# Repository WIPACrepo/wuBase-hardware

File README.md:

# wuBase-hardware
Hardware design files for wuBase photosensor control and readout board developed for IceCube Neutrino Observatory

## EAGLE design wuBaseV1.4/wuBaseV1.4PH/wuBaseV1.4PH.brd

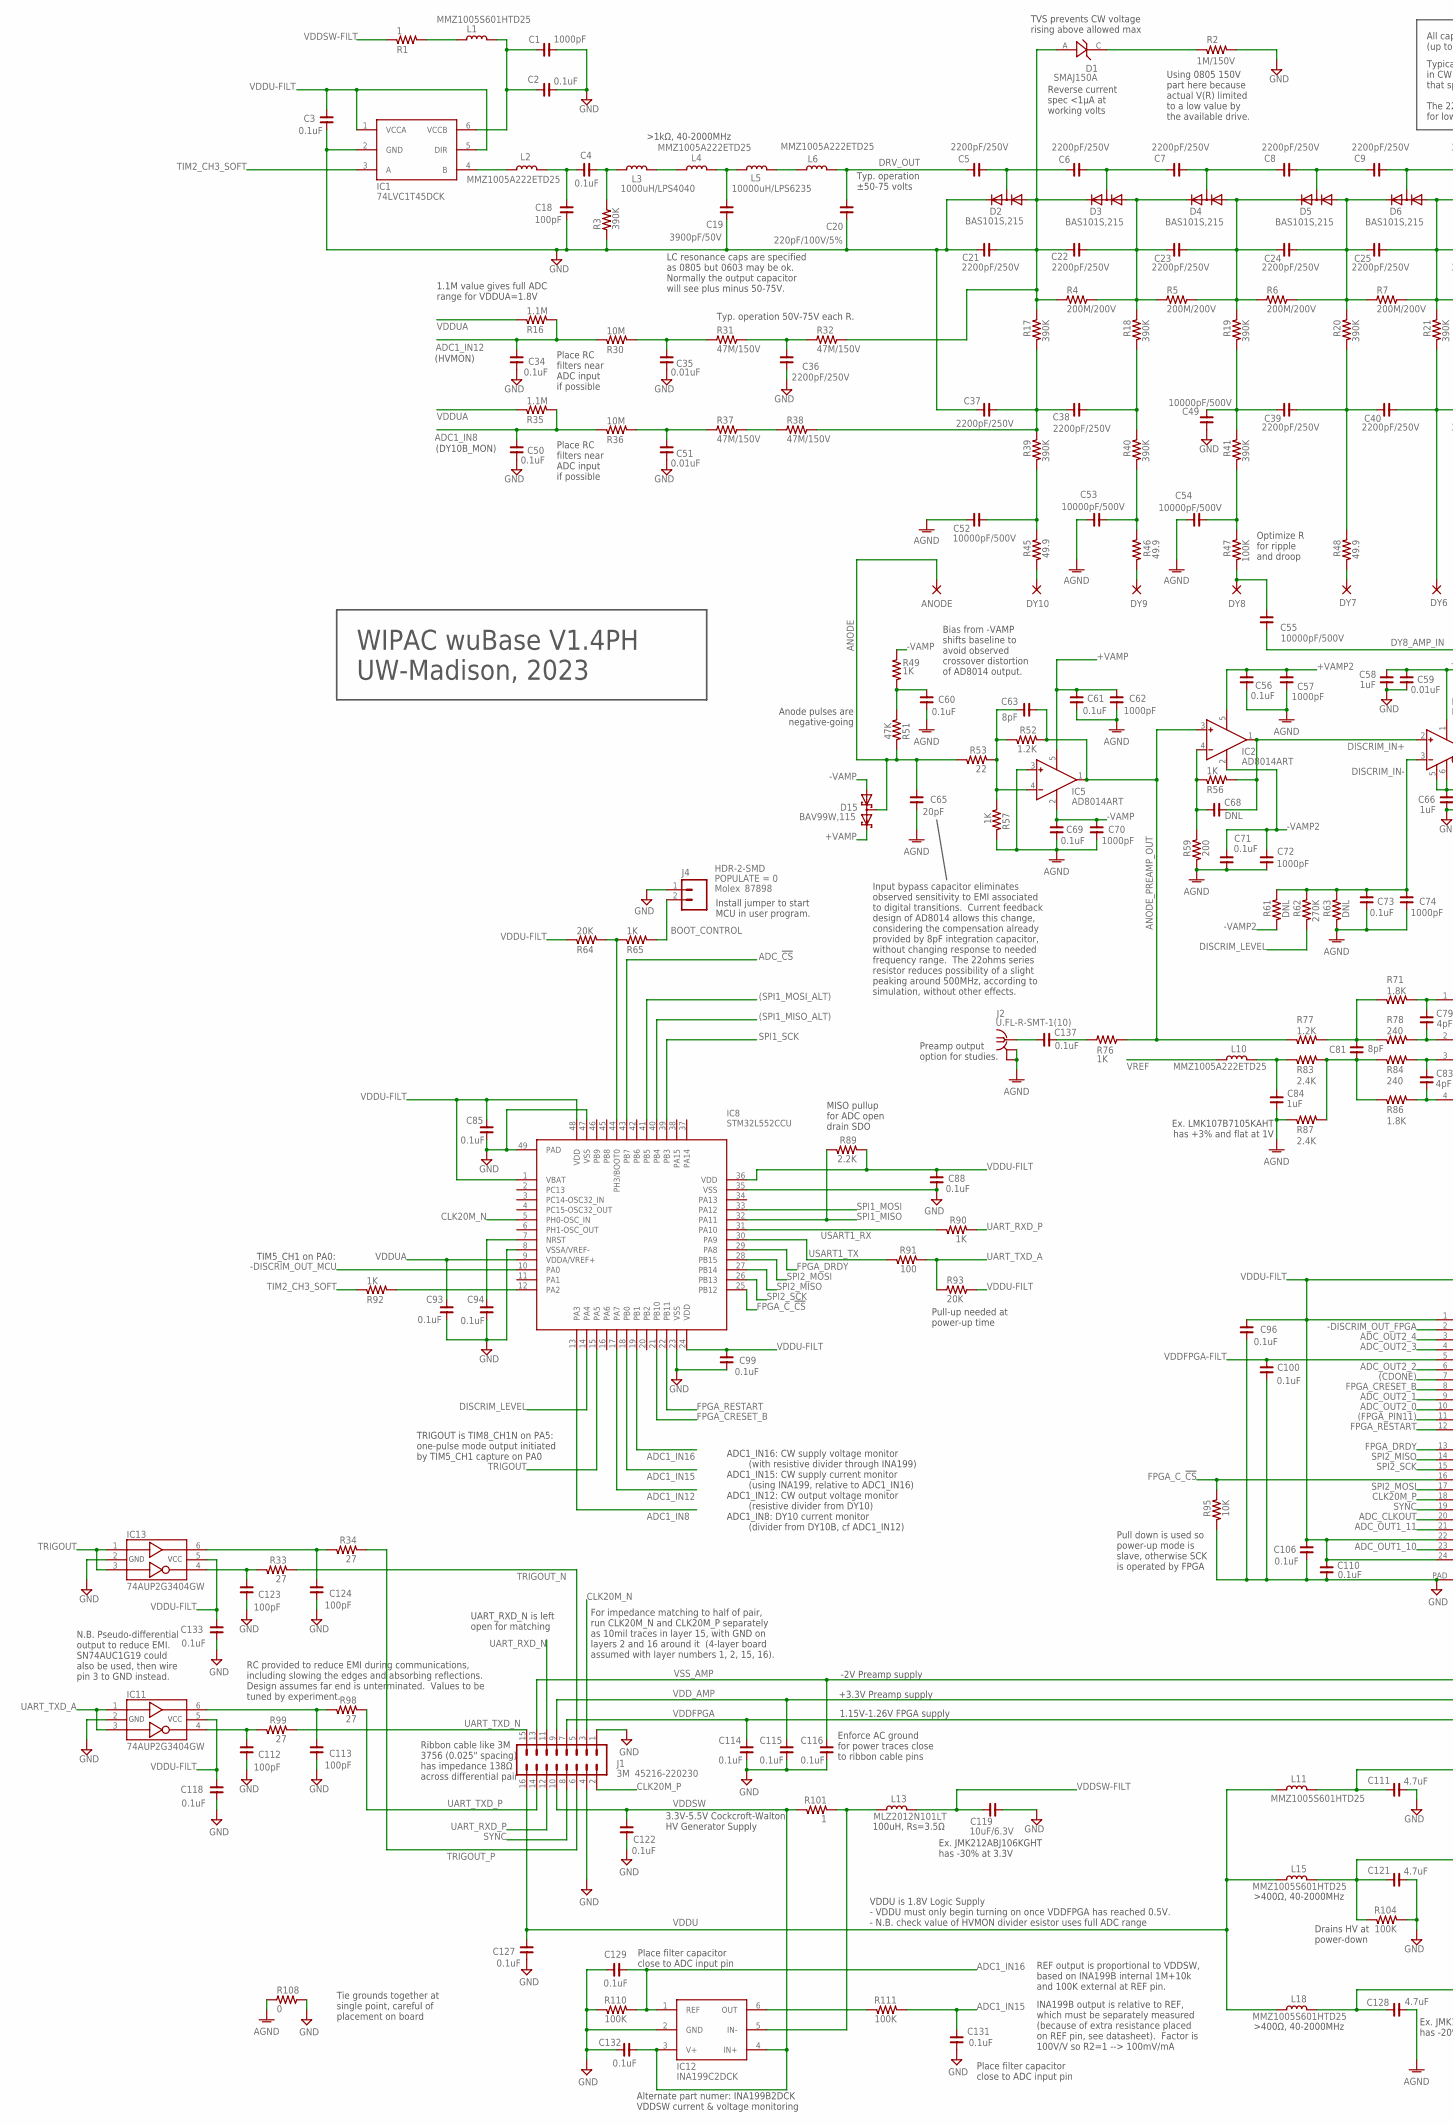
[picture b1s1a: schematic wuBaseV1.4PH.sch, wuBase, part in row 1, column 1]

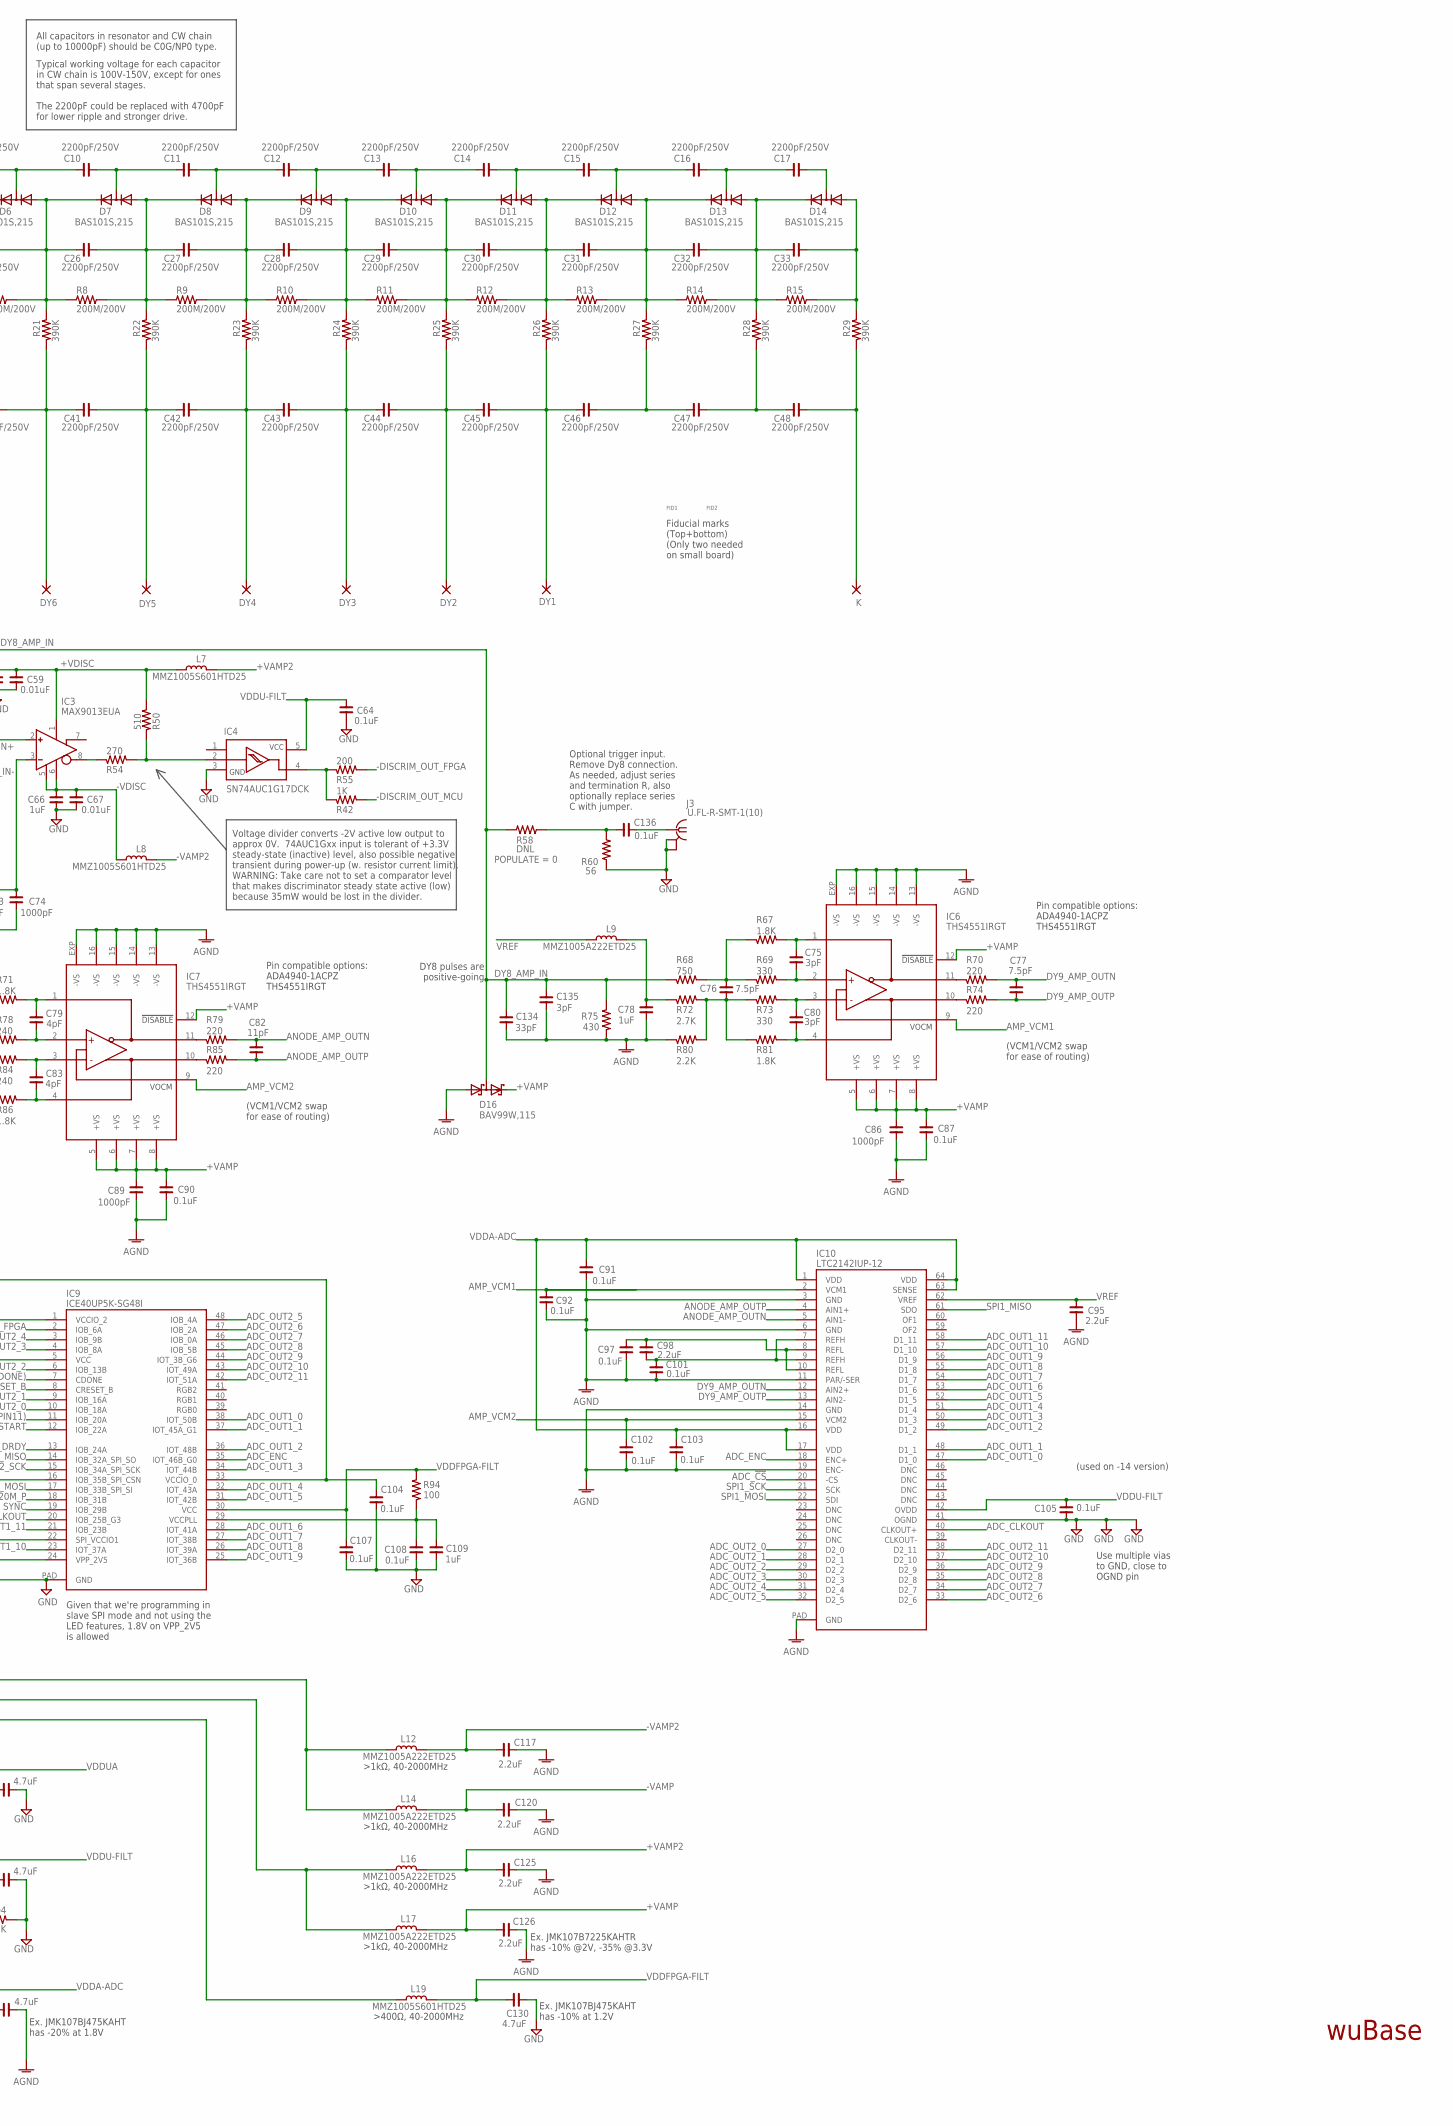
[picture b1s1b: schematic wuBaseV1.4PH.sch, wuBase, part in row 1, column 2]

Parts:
ANODE: PAD-0430-BARE; 0430-BARE
C1, C57, C62, C70, C72, C74, C86, C89: 1000pF; C0402; MPN GCM155R71H102KA37D
C2, C3, C34, C50, C56, C60, C61, C64, C69, C71, C73, C85, C87, C88, C90, C91, C92, C93, C94, C96, C97, C99, C100, C101, C102, C103, C104, C105, C106, C107, C108, C110, C114, C115, C116, C118, C122, C127, C129, C131, C132, C133, C136, C137: 0.1uF; C0402; MPN GCM155R71C104KA55D
C4: 0.1uF; C0402-HV; MPN GCM155R71C104KA55D
C5, C6, C7, C8, C9, C10, C11, C12, C13, C14, C15, C16, C17, C21, C22, C23, C24, C25, C26, C27, C28, C29, C30, C31, C32, C33, C36, C37, C38, C39, C40, C41, C42, C43, C44, C45, C46, C47, C48: 2200pF/250V; C0805-HV; MPN C0805C222JAGACAUTO
C18: 100pF; C0402-HV; MPN C0402C101J3GACAUTO
C19: 3900pF/50V; C0805-HV; MPN CGA4C2C0G1H392J060AA
C20: 220pF/100V/5%; C0805-HV; MPN C0805C221J1GACAUTO
C35, C51, C59, C67: 0.01uF; C0402; MPN CGA2B2X5R1E103K050BA
C49, C52, C53, C54, C55: 10000pF/500V; C1206-HV; MPN CGA5L4NP02J103J160AA
C58, C66, C78, C84, C109: 1uF; C0603; MPN LMK107B7105KAHT
C63, C81: 8pF; C0402; MPN GCM1555C1H8R0BA16D
C65: 20pF; C0402; MPN GCM1555C1H200JA16D
C68: DNL; C0402
C75, C80, C135: 3pF; C0402; MPN GCM1555C1H3R0BA16D
C76, C77: 7.5pF; C0402; MPN GCQ1555C1H7R5BB01D
C79, C83: 4pF; C0402; MPN GCM1555C1H4R0BA16D
C82: 11pF; C0402; MPN GCM1555C1H110FA16D
C95, C98, C117, C120, C125, C126: 2.2uF; C0603; MPN CGA3E1X7R0J225K080AC
C111, C121, C128, C130: 4.7uF; C0603; MPN JMK107BJ475KAHT
C112, C113, C123, C124: 100pF; C0402; MPN C0402C101J3GACAUTO
C119: 10uF/6.3V; C0805; MPN C0805C106K8PACTU
C134: 33pF; C0402; MPN GCM1555C1H330FA16D
D1: SMAJ150A; DO214AC-HV; MPN SMAJ150A
D2, D3, D4, D5, D6, D7, D8, D9, D10, D11, D12, D13, D14: BAS101S,215; SOT23-ROUNDED; MPN BAS101S,215
D15, D16: BAV99W,115; SC70-3L; MPN BAV99W,115
DY1, DY2, DY3, DY4, DY5, DY6, DY7, DY8, DY9, DY10: PAD-0430-BARE; 0430-BARE
FID1, FID2: FIDUCIAL_0.5MM
IC1: 74LVC1T45DCK; SC70-6L-TI; MPN 74LVC1T45GW-Q100H
IC2, IC5: AD8014ART; SOT23-5; MPN AD8014ARTZ-REEL7
IC3: MAX9013EUA; MSOP8; MPN MAX9013EUA+
IC4: SN74AUC1G17DCK; SC70-5L-TI; MPN SN74AUC1G17DCKR
IC6, IC7: THS4551IRGT; LFCSP16; MPN THS4551IRGTR
IC8: STM32L552CCU; UFQFPN48-STMICRO; MPN STM32L552CCU6
IC9: ICE40UP5K-SG48I; QFN48-ICE40ULTRA; MPN ICE40UP5K-SG48I
IC10: LTC2142IUP-12; QFN64-LTC214X; MPN LTC2141IUP-12
IC11, IC13: 74AUP2G3404GW; SC70-6L-TI; MPN 74AUP2G3404GW,125
IC12: INA199C2DCK; SC70-6L-TI; MPN INA199C2DCKR
J1: HDR-16; 3M-45216-220230; MPN 45216-220230
J2, J3: COAX-2GNDU.FL; HIROSE_U.FL-R-SMT-1; MPN U.FL-R-SMT-1(10)
J4: HDR-2-SMD; HEADER-SMD-2X1-MINIMUM; MPN 87898
K: PAD-0430-BARE; 0430-BARE
L1, L7, L8, L11, L15, L18, L19: MMZ1005S601HTD25; L0402; MPN MMZ1005S601ETD25
L2, L4, L6: MMZ1005A222ETD25; L0402-HV; MPN MMZ1005A222ETD25
L3: 1000uH/LPS4040; LPS4040-REDUCED; MPN LPS4040-105MRC
L5: 10000uH/LPS6235; LPS6235-REDUCED; MPN LPS6235-106MRC
L9, L10, L12, L14, L16, L17: MMZ1005A222ETD25; L0402; MPN MMZ1005A222ETD25
L13: MLZ2012N101LT; L0805; MPN MLZ2012N101LTD25
R1, R101: 1; R0402; MPN AC0402FR-071RL
R2: 1M/150V; R0805-HV; MPN AC0805FR-071ML
R3, R17, R18, R19, R20, R21, R22, R23, R24, R25, R26, R27, R28, R29, R39, R40, R41: 390K; R0402-HV; MPN AC0402FR-07390KL
R4, R5, R6, R7, R8, R9, R10, R11, R12, R13, R14, R15: 200M/200V; R1206-HV; MPN CRCW1206200MJPEAHR
R16, R35: 1.1M; R0402; MPN AC0402FR-071M1L
R30, R36: 10M; R0402; MPN AC0402FR-0710ML
R31, R32, R37, R38: 47M/150V; R0805-HV; MPN RC0805JR-0747ML
R33, R34, R98, R99: 27; R0402; MPN AC0402FR-0727RL
R42, R49, R56, R57, R65, R76, R90, R92: 1K; R0402; MPN AC0402FR-071KL
R45, R46, R48: 49.9; R0402-HV; MPN AC0402FR-0749R9L
R47: 100K; R0402-HV; MPN AC0402FR-07100KL
R50: 510; R0402; MPN AC0402FR-07510RL
R51: 47K; R0402; MPN AC0402FR-0747KL
R52, R77: 1.2K; R0402; MPN AC0402FR-071K2L
R53: 22; R0402; MPN AC0402FR-0722RL
R54: 270; R0402; MPN AC0402FR-07270RL
R55, R59: 200; R0402; MPN AC0402FR-07200RL
R58, R61, R63: DNL; R0402
R60: 56; R0402; MPN AC0402FR-0756RL
R62: 270K; R0402; MPN AC0402FR-07270KL
R64, R93: 20K; R0402; MPN AC0402FR-0720KL
R67, R71, R81, R86: 1.8K; R0402; MPN AC0402FR-071K8L
R68: 750; R0402; MPN AC0402FR-07750RL
R69, R73: 330; R0402; MPN AC0402FR-07330RL
R70, R74, R79, R85: 220; R0402; MPN AC0402FR-07220RL
R72: 2.7K; R0402; MPN AC0402FR-072K7L
R75: 430; R0402; MPN AC0402FR-07430RL
R78, R84: 240; R0402; MPN AC0402FR-07240RL
R80, R89: 2.2K; R0402; MPN AC0402FR-072K2L
R83, R87: 2.4K; R0402; MPN AC0402FR-072K4L
R91, R94: 100; R0402; MPN AC0402FR-07100RL
R95: 10K; R0402; MPN AC0402FR-0710KL
R104, R110, R111: 100K; R0402; MPN AC0402FR-07100KL
R108: 0; R0402; MPN RC0402JR-070RL

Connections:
(CDONE): IC9.7 (CDONE)
(FPGA_PIN11): IC9.11 (IOB_20A)
(SPI1_MISO_ALT): IC8.40 (PB4)
(SPI1_MOSI_ALT): IC8.41 (PB5)
+VAMP: C61.1, C62.1, C86.1, C87.1, C89.1, C90.1, C126.2, D15.2 (C2), D16.2 (C2), IC5.5 (V+), IC6.5 (+VS), IC6.6 (+VS), IC6.7 (+VS), IC6.8 (+VS), IC6.12 (!DISABLE), IC7.5 (+VS), IC7.6 (+VS), IC7.7 (+VS), IC7.8 (+VS), IC7.12 (!DISABLE), L17.2
+VAMP2: C56.1, C57.1, C125.2, IC2.5 (V+), L7.2, L16.2
+VDISC: C58.1, C59.1, IC3.1 (VCC), L7.1, R50.2
-DISCRIM_BUFOUT: IC4.4 (OUT), R42.1, R55.1
-DISCRIM_OUT: IC3.8 (QBAR), R54.1
-DISCRIM_OUT_DIVIDER: IC4.2 (IN), R50.1, R54.2
-DISCRIM_OUT_FPGA: IC9.2 (IOB_6A), R55.2
-DISCRIM_OUT_MCU: IC8.10 (PA0), R42.2
-VAMP: C69.1, C70.1, C120.2, D15.1 (A1), IC5.2 (V-), L14.2, R49.1
-VAMP2: C71.1, C72.1, C117.2, IC2.2 (V-), L8.2, L12.2, R61.2
-VDISC: C66.1, C67.1, IC3.5 (LE), IC3.6 (GND), L8.1
ADC1_IN8: C50.1, IC8.13 (PA3), R35.2, R36.1
ADC1_IN12: C34.1, IC8.17 (PA7), R16.2, R30.1
ADC1_IN15: C131.2, IC8.18 (PB0), R111.1
ADC1_IN16: C129.2, IC8.19 (PB1), IC12.1 (REF), R110.1
ADC_!CS: IC8.43 (PB7), IC10.20 (-CS)
ADC_CLKOUT: IC9.20 (IOB_25B_G3), IC10.40 (CLKOUT+)
ADC_ENC: IC9.35 (IOT_46B_G0), IC10.18 (ENC+)
ADC_OUT1_0: IC9.38 (IOT_50B), IC10.47 (D1_0)
ADC_OUT1_1: IC9.37 (IOT_45A_G1), IC10.48 (D1_1)
ADC_OUT1_2: IC9.36 (IOT_48B), IC10.49 (D1_2)
ADC_OUT1_3: IC9.34 (IOT_44B), IC10.50 (D1_3)
ADC_OUT1_4: IC9.32 (IOT_43A), IC10.51 (D1_4)
ADC_OUT1_5: IC9.31 (IOT_42B), IC10.52 (D1_5)
ADC_OUT1_6: IC9.28 (IOT_41A), IC10.53 (D1_6)
ADC_OUT1_7: IC9.27 (IOT_38B), IC10.54 (D1_7)
ADC_OUT1_8: IC9.26 (IOT_39A), IC10.55 (D1_8)
ADC_OUT1_9: IC9.25 (IOT_36B), IC10.56 (D1_9)
ADC_OUT1_10: IC9.23 (IOT_37A), IC10.57 (D1_10)
ADC_OUT1_11: IC9.21 (IOB_23B), IC10.58 (D1_11)
ADC_OUT2_0: IC9.10 (IOB_18A), IC10.27 (D2_0)
ADC_OUT2_1: IC9.9 (IOB_16A), IC10.28 (D2_1)
ADC_OUT2_2: IC9.6 (IOB_13B), IC10.29 (D2_2)
ADC_OUT2_3: IC9.4 (IOB_8A), IC10.30 (D2_3)
ADC_OUT2_4: IC9.3 (IOB_9B), IC10.31 (D2_4)
ADC_OUT2_5: IC9.48 (IOB_4A), IC10.32 (D2_5)
ADC_OUT2_6: IC9.47 (IOB_2A), IC10.33 (D2_6)
ADC_OUT2_7: IC9.46 (IOB_0A), IC10.34 (D2_7)
ADC_OUT2_8: IC9.45 (IOB_5B), IC10.35 (D2_8)
ADC_OUT2_9: IC9.44 (IOT_3B_G6), IC10.36 (D2_9)
ADC_OUT2_10: IC9.43 (IOT_49A), IC10.37 (D2_10)
ADC_OUT2_11: IC9.42 (IOT_51A), IC10.38 (D2_11)
AGND: C52.1, C53.2, C54.2, C56.2, C57.2, C60.2, C61.2, C62.2, C65.2, C69.2, C70.2, C71.2, C72.2, C73.2, C74.2, C78.2, C84.2, C86.2, C87.2, C89.2, C90.2, C91.2, C92.2, C95.2, C97.2, C101.2, C102.2, C103.2, C117.1, C120.1, C125.1, C126.1, C128.1, C134.2, C135.2, D16.1 (A1), IC5.3 (IN+), IC6.13 (-VS), IC6.14 (-VS), IC6.15 (-VS), IC6.16 (-VS), IC6.EXP (-VS), IC7.13 (-VS), IC7.14 (-VS), IC7.15 (-VS), IC7.16 (-VS), IC7.EXP (-VS), IC10.3 (GND), IC10.6 (GND), IC10.11 (PAR/-SER), IC10.14 (GND), IC10.19 (ENC-), IC10.PAD (GND), J2.2 (GND), J2.3 (GND), R57.2, R59.2, R63.2, R75.1, R80.1, R87.1, R108.1
AMP1_INM: C63.1, IC5.4 (IN-), R52.2, R53.1, R57.1
AMP2_INM: C68.1, IC2.4 (IN-), R56.1, R59.1
AMP_VCM1: C92.1, IC6.9 (VOCM), IC10.2 (VCM1)
AMP_VCM2: C102.1, IC7.9 (VOCM), IC10.15 (VCM2)
ANODE: ANODE.P$1, C65.1, D15.3 (C1A2), R51.2, R53.2
ANODE_AMP_OUTN: C82.1, IC10.5 (AIN1-), R79.2
ANODE_AMP_OUTP: C82.2, IC10.4 (AIN1+), R85.2
ANODE_PREAMP_OUT: C63.2, IC2.3 (IN+), IC5.1 (OUT), R52.1, R76.1, R77.1
BIAS_FILT: C60.1, R49.2, R51.1
BOOT0: IC8.44 (PH3/BOOT0), R64.2, R65.1
BOOT_CONTROL: J4.2, R65.2
CH1COAX: C137.1, J2.1 (SIGNAL)
CH1COAX_DC: C137.2, R76.2
CH2COAX: C136.2, J3.1 (SIGNAL)
CH2COAX_DC: C136.1, R58.1, R60.1
CLK20M_N: IC8.5 (PH0-OSC_IN), J1.3
CLK20M_P: IC9.18 (IOB_31B), J1.2
CW_1_KB: C15.2, C16.1, D12.3 (C1A2)
CW_2_1: C14.2, C15.1, D11.3 (C1A2)
CW_3_2: C13.2, C14.1, D10.3 (C1A2)
CW_4_3: C12.2, C13.1, D9.3 (C1A2)
CW_5_4: C11.2, C12.1, D8.3 (C1A2)
CW_6_5: C10.2, C11.1, D7.3 (C1A2)
CW_7_6: C9.2, C10.1, D6.3 (C1A2)
CW_8_7: C8.2, C9.1, D5.3 (C1A2)
CW_9_8: C7.2, C8.1, D4.3 (C1A2)
CW_10_9: C6.2, C7.1, D3.3 (C1A2)
CW_A_10: C5.2, C6.1, D2.3 (C1A2)
CW_KA_K: C17.2, D14.3 (C1A2)
CW_KB_KA: C16.2, C17.1, D13.3 (C1A2)
DISCRIM_IN+: C68.2, IC2.1 (OUT), IC3.2 (IN+), R56.2
DISCRIM_IN-: C73.1, C74.1, IC3.3 (IN-), R61.1, R62.1, R63.1
DISCRIM_LEVEL: IC8.14 (PA4), R62.2
DRV_FILT: C4.2, C18.1, L2.2
DRV_L1INP: C4.1, L3.2, R3.2
DRV_L1OUT: L3.1, L4.1
DRV_L2INP: C19.1, L4.2, L5.2
DRV_L2OUT: L5.1, L6.2
DRV_OUT: C5.1, C20.1, L6.1
DRV_SQUARE: IC1.4 (B), L2.1
DY1: C45.2, C46.1, DY1.P$1, R26.2
DY1A: C30.2, C31.1, D11.1 (A1), D12.2 (C2), R12.2, R13.1, R26.1
DY2: C44.2, C45.1, DY2.P$1, R25.2
DY2A: C29.2, C30.1, D10.1 (A1), D11.2 (C2), R11.2, R12.1, R25.1
DY3: C43.2, C44.1, DY3.P$1, R24.2
DY3A: C28.2, C29.1, D9.1 (A1), D10.2 (C2), R10.2, R11.1, R24.1
DY4: C42.2, C43.1, DY4.P$1, R23.2
DY4A: C27.2, C28.1, D8.1 (A1), D9.2 (C2), R9.2, R10.1, R23.1
DY5: C41.2, C42.1, DY5.P$1, R22.2
DY5A: C26.2, C27.1, D7.1 (A1), D8.2 (C2), R8.2, R9.1, R22.1
DY6: C40.2, C41.1, DY6.P$1, R21.2
DY6A: C25.2, C26.1, D6.1 (A1), D7.2 (C2), R7.2, R8.1, R21.1
DY7: DY7.P$1, R48.2
DY7A: C24.2, C25.1, D5.1 (A1), D6.2 (C2), R6.2, R7.1, R20.1
DY7B: C39.2, C40.1, R20.2, R48.1
DY8: C55.1, DY8.P$1, R47.2
DY8A: C23.2, C24.1, D4.1 (A1), D5.2 (C2), R5.2, R6.1, R19.1
DY8B: C39.1, C49.1, R19.2, R41.1
DY8C: C54.1, R41.2, R47.1
DY8_AMP_IN: C55.2, C134.1, C135.1, D16.3 (C1A2), R58.2, R68.1, R75.2
DY9: DY9.P$1, R46.2
DY9A: C22.2, C23.1, D3.1 (A1), D4.2 (C2), R4.2, R5.1, R18.1
DY9B: C38.2, R18.2, R40.1
DY9C: C53.1, R40.2, R46.1
DY9_AMP_OUTN: C77.1, IC10.12 (AIN2+), R70.2
DY9_AMP_OUTP: C77.2, IC10.13 (AIN2-), R74.2
DY10: DY10.P$1, R45.2
DY10A: C21.2, C22.1, D1.A, D2.1 (A1), D3.2 (C2), R4.1, R17.1, R32.2
DY10B: C37.2, C38.1, R17.2, R38.2, R39.1
DY10B_MON_A: R37.2, R38.1
DY10B_MON_B: C51.1, R36.2, R37.1
DY10C: C52.2, R39.2, R45.1
FPGA_CRESET_B: IC8.21 (PB10), IC9.8 (CRESET_B)
FPGA_C_!CS: IC8.25 (PB12), IC9.16 (IOB_35B_SPI_CSN), R95.1
FPGA_DRDY: IC8.29 (PA8), IC9.13 (IOB_24A)
FPGA_RESTART: IC8.22 (PB11), IC9.12 (IOB_22A)
GND: C1.1, C2.1, C3.1, C18.2, C19.2, C20.2, C21.1, C34.2, C35.2, C36.2, C37.1, C49.2, C50.2, C51.2, C58.2, C59.2, C64.1, C66.2, C67.2, C85.2, C88.2, C93.2, C94.2, C96.2, C99.2, C100.2, C104.2, C105.2, C106.2, C107.2, C108.2, C109.2, C110.2, C111.1, C112.2, C113.2, C114.2, C115.2, C116.2, C118.2, C119.2, C121.1, C122.2, C123.2, C124.2, C127.2, C129.1, C130.2, C131.1, C132.1, C133.2, D2.2 (C2), IC1.2 (GND), IC4.3 (GND), IC8.8 (VSSA/VREF-), IC8.23 (VSS), IC8.35 (VSS), IC8.47 (VSS), IC8.49 (PAD), IC9.PAD (GND), IC10.41 (OGND), IC11.2 (GND), IC12.2 (GND), IC13.2 (GND), J1.1, J1.4, J3.2 (GND), J3.3 (GND), J4.1, R2.1, R3.1, R60.2, R95.2, R104.1, R108.2, R110.2
HVMON_A: C36.1, R31.2, R32.1
HVMON_B: C35.1, R30.2, R31.1
K: C48.2, K.P$1, R29.2
K-DY1-AA: C32.2, C33.1, D13.1 (A1), D14.2 (C2), R14.2, R15.1, R28.1
K-DY1-AB: C47.2, C48.1, R28.2
K-DY1-BA: C31.2, C32.1, D12.1 (A1), D13.2 (C2), R13.2, R14.1, R27.1
K-DY1-BB: C46.2, C47.1, R27.2
KA: C33.2, D14.1 (A1), R15.2, R29.1
unnamed: C79.2, IC7.2 (+IN), R78.2
unnamed: C83.1, IC7.3 (-IN), R84.2
unnamed: C81.2, R83.2, R84.1, R86.1, R87.2
unnamed: C81.1, R71.1, R77.2, R78.1
unnamed: C79.1, IC7.1 (-FB), R71.2
unnamed: C83.2, IC7.4 (+FB), R86.2
unnamed: IC7.11 (-OUT), R79.1
unnamed: IC7.10 (+OUT), R85.1
unnamed: C75.2, IC6.2 (+IN), R69.2
unnamed: C80.1, IC6.3 (-IN), R73.2
unnamed: C76.1, R67.1, R68.2, R69.1
unnamed: C76.2, R72.2, R73.1, R80.2, R81.1
unnamed: C75.1, IC6.1 (-FB), R67.2
unnamed: C80.2, IC6.4 (+FB), R81.2
unnamed: IC6.11 (-OUT), R70.1
unnamed: IC6.10 (+OUT), R74.1
NRST: C94.1, IC8.7 (NRST)
REFH: C98.2, C101.1, IC10.7 (REFH), IC10.9 (REFH)
REFL: C97.1, C98.1, IC10.8 (REFL), IC10.10 (REFL)
SPI1_MISO: IC8.32 (PA11), IC10.61 (SDO), R89.2
SPI1_MOSI: IC8.33 (PA12), IC10.22 (SDI)
SPI1_SCK: IC8.39 (PB3), IC10.21 (SCK)
SPI2_MISO: IC8.27 (PB14), IC9.14 (IOB_32A_SPI_SO)
SPI2_MOSI: IC8.28 (PB15), IC9.17 (IOB_33B_SPI_SI)
SPI2_SCK: IC8.26 (PB13), IC9.15 (IOB_34A_SPI_SCK)
SYNC: IC9.19 (IOB_29B), J1.8
TIM2_CH3: IC8.12 (PA2), R92.2
TIM2_CH3_SOFT: IC1.3 (A), R92.1
TRIGOUT: IC8.15 (PA5), IC13.1 (1A), IC13.3 (2A)
TRIGOUT_N: J1.5, R33.1
TRIGOUT_NA: C123.1, IC13.4 (2Y), R33.2
TRIGOUT_P: J1.6, R34.1
TRIGOUT_PA: C124.1, IC13.6 (1Y), R34.2
TVS_OUT: D1.C, R2.2
UART_RXD_N: J1.11
UART_RXD_P: J1.12, R90.1
UART_TXD_A: IC11.1 (1A), IC11.3 (2A), R91.1, R93.1
UART_TXD_N: J1.15, R99.1
UART_TXD_NA: C112.1, IC11.4 (2Y), R99.2
UART_TXD_P: J1.14, R98.1
UART_TXD_PA: C113.1, IC11.6 (1Y), R98.2
USART1_RX: IC8.31 (PA10), R90.2
USART1_TX: IC8.30 (PA9), R91.2
VCCPLL: C108.1, C109.1, IC9.29 (VCCPLL), R94.2
VDDA-ADC: C91.1, C103.1, C128.2, IC10.1 (VDD), IC10.16 (VDD), IC10.17 (VDD), IC10.63 (SENSE), IC10.64 (VDD), L18.2
VDDFPGA: C114.1, J1.7, L19.1
VDDFPGA-FILT: C100.1, C107.1, C130.1, IC9.5 (VCC), IC9.30 (VCC), L19.2, R94.1
VDDSW: C122.1, C132.2, IC12.3 (V+), IC12.4 (IN+), J1.10, R101.2
VDDSW-FILT: C119.1, L13.2, R1.1
VDDSW-FILT-RL: L1.2, R1.2
VDDSW-FINAL: C1.2, C2.2, IC1.6 (VCCB), L1.1
VDDSW-RL: IC12.5 (IN-), L13.1, R101.1
VDDSW_IMON: IC12.6 (OUT), R111.2
VDDU: C127.1, J1.16, L11.1, L15.1, L18.1
VDDU-FILT: C3.2, C64.2, C85.1, C88.1, C96.1, C99.1, C104.1, C105.1, C106.1, C110.1, C118.1, C121.2, C133.1, IC1.1 (VCCA), IC1.5 (DIR), IC4.5 (VCC), IC8.1 (VBAT), IC8.24 (VDD), IC8.36 (VDD), IC8.48 (VDD), IC9.1 (VCCIO_2), IC9.22 (SPI_VCCIO1), IC9.24 (VPP_2V5), IC9.33 (VCCIO_0), IC10.42 (OVDD), IC11.5 (VCC), IC13.5 (VCC), L15.2, R64.1, R89.1, R93.2, R104.2
VDDUA: C93.1, C111.2, IC8.9 (VDDA/VREF+), L11.2, R16.1, R35.1
VDD_AMP: C115.1, J1.9, L16.1, L17.1
VREF: C95.1, IC10.62 (VREF), L9.1, L10.1
VREF_FILT1: C84.1, L10.2, R83.1
VREF_FILT2: C78.1, L9.2, R72.1
VSS_AMP: C116.1, J1.13, L12.1, L14.1

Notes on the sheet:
Fiducial marks (Top+bottom) (Only two needed on small board)
VDDU is 1.8V Logic Supply - VDDU must only begin turning on once VDDFPGA has reached 0.5V. - N.B. check value of HVMON divider esistor uses full ADC range
3.3V-5.5V Cockcroft-Walton HV Generator Supply
(HVMON)
INA199B output is relative to REF, which must be separately measured (because of extra resistance placed on REF pin, see datasheet). Factor is 100V/V so R2=1 --> 100mV/mA
ADC1_IN16: CW supply voltage monitor (with resistive divider through INA199) ADC1_IN15: CW supply current monitor (using INA199, relative to ADC1_IN16) ADC1_IN12: CW output voltage monitor (resistive divider from DY10) ADC1_IN8: DY10 current monitor (divider from DY10B, cf ADC1_IN12)
REF output is proportional to VDDSW, based on INA199B internal 1M+10k and 100K external at REF pin.
Place filter capacitor close to ADC input pin
Alternate part numer: INA199B2DCK VDDSW current & voltage monitoring
100uH, Rs=3.5Ω
WIPAC wuBase V1.4PH UW-Madison, 2023
TVS prevents CW voltage rising above allowed max
Place RC filters near ADC input if possible
Typ. operation 50V-75V each R.
Typ. operation ±50-75 volts
Drains HV at power-down
Typical working voltage for each capacitor in CW chain is 100V-150V, except for ones that span several stages. The 2200pF could be replaced with 4700pF for lower ripple and stronger drive.
All capacitors in resonator and CW chain (up to 10000pF) should be C0G/NP0 type.
LC resonance caps are specified as 0805 but 0603 may be ok. Normally the output capacitor will see plus minus 50-75V.
RC provided to reduce EMI during communications, including slowing the edges and absorbing reflections. Design assumes far end is unterminated. Values to be tuned by experiment.
Using 0805 150V part here because actual V(R) limited to a low value by the available drive.
Reverse current spec <1µA at working volts
Install jumper to start MCU in user program.
1.1M value gives full ADC range for VDDUA=1.8V
1.15V-1.26V FPGA supply
Given that we're programming in slave SPI mode and not using the LED features, 1.8V on VPP_2V5 is allowed
+3.3V Preamp supply
-2V Preamp supply
Optimize R for ripple and droop
Tie grounds together at single point, careful of placement on board
Voltage divider converts -2V active low output to approx 0V. 74AUC1Gxx input is tolerant of +3.3V steady-state (inactive) level, also possible negative transient during power-up (w. resistor current limit). WARNING: Take care not to set a comparator level that makes discriminator steady state activ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
Enforce AC ground for power traces close to ribbon cable pins
N.B. Pseudo-differential output to reduce EMI. SN74AUC1G19 could also be used, then wire pin 3 to GND instead.
MISO pullup for ADC open drain SDO
(DY10B_MON)
DY8 pulses are positive-going
Anode pulses are negative-going
Ex. JMK107BJ475KAHT has -10% at 1.2V
Ex. JMK107BJ475KAHT has -20% at 1.8V
Ex. JMK107B7225KAHTR has -10% @2V, -35% @3.3V

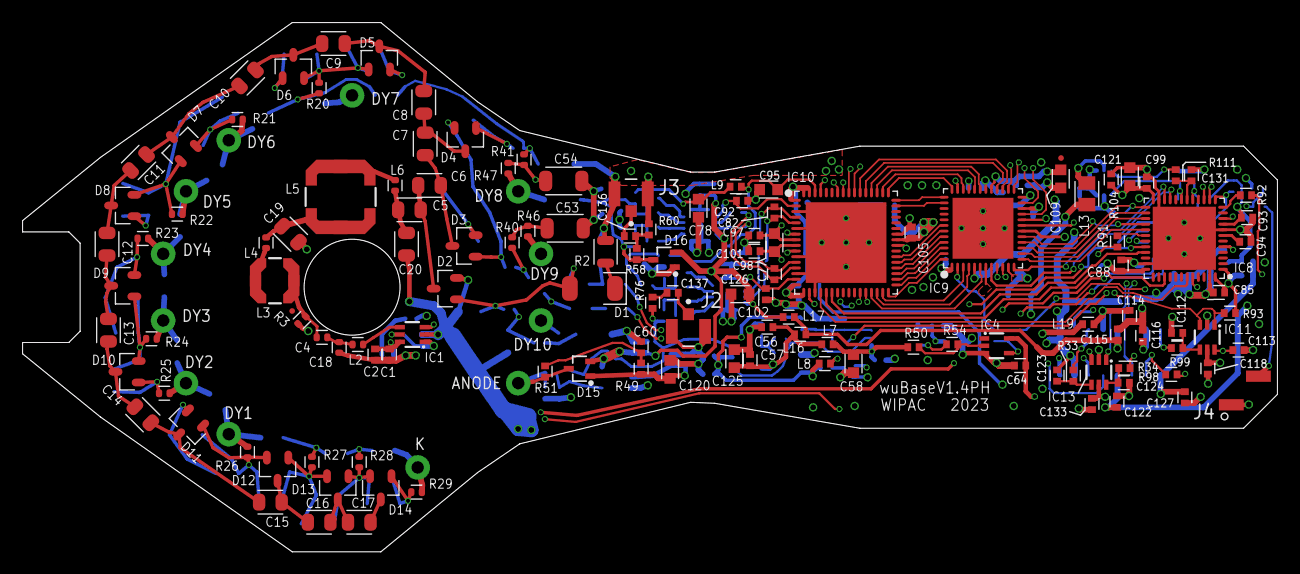
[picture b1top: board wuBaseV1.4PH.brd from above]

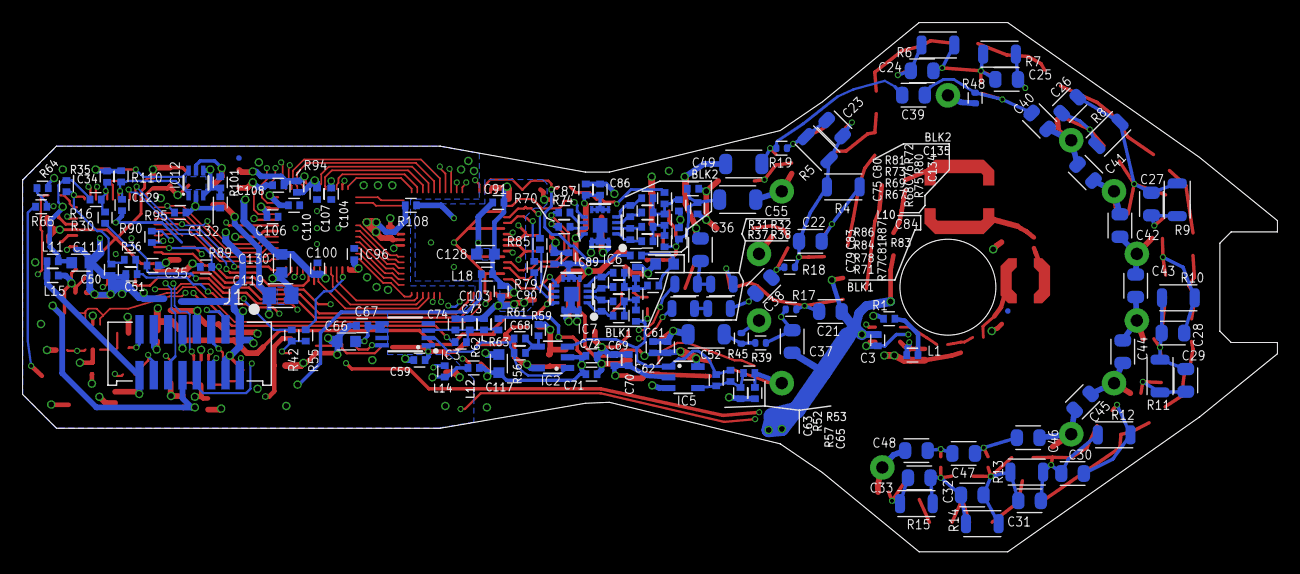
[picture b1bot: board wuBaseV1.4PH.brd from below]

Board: 4 copper layers, 111.2 x 46.9 mm, 300 parts (168 on the bottom side), 188 nets.

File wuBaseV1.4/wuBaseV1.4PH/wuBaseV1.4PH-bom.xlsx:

Qty | Value | Package | Parts | Description | MFG | MPN | POPULATE
1 | 0 | R0402 | R108 | Resistor |  | RC0402JR-070RL | 1
4 | 0.01uF | C0402 | C35, C51, C59, C67 | Capacitor |  | CGA2B2X5R1E103K050BA | 1
45 | 0.1uF | C0402 | C2, C3, C4, C34, C50, C56, C60, C61, C64, C69, C71, C73, C85, C87, C88, C90, C9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 | Capacitor |  | GCM155R71C104KA55D | 1
2 | 1 | R0402 | R1, R101 | Resistor |  | AC0402FR-071RL | 1
2 | 1.1M | R0402 | R16, R35 | Resistor |  | AC0402FR-071M1L | 1
2 | 1.2K | R0402 | R52, R77 | Resistor |  | AC0402FR-071K2L | 1
4 | 1.8K | R0402 | R67, R71, R81, R86 | Resistor |  | AC0402FR-071K8L | 1
2 | 100 | R0402 | R91, R94 | Resistor |  | AC0402FR-07100RL | 1
5 | 10000pF/500V | C1206 | C49, C52, C53, C54, C55 | Capacitor |  | CGA5L4NP02J103J160AA | 1
1 | 10000uH/LPS6235 | LPS6235 | L5 | Inductor |  | LPS6235-106MRC | 1
8 | 1000pF | C0402 | C1, C57, C62, C70, C72, C74, C86, C89 | Capacitor |  | GCM155R71H102KA37D | 1
1 | 1000uH/LPS4040 | LPS4040 | L3 | Inductor |  | LPS4040-105MRC | 1
4 | 100K | R0402 | R47, R104, R110, R111 | Resistor |  | AC0402FR-07100KL | 1
5 | 100pF | C0402 | C18, C112, C113, C123, C124 | Capacitor |  | C0402C101J3GACAUTO | 1
1 | 10K | R0402 | R95 | Resistor |  | AC0402FR-0710KL | 1
2 | 10M | R0402 | R30, R36 | Resistor |  | AC0402FR-0710ML | 1
1 | 10uF/6.3V | C0805 | C119 | Capacitor |  | C0805C106K8PACTU | 1
1 | 11pF | C0402 | C82 | Capacitor |  | GCM1555C1H110FA16D | 1
8 | 1K | R0402 | R42, R49, R56, R57, R65, R76, R90, R92 | Resistor |  | AC0402FR-071KL | 1
1 | 1M/150V | R0805 | R2 | Resistor |  | AC0805FR-071ML | 1
5 | 1uF | C0603 | C58, C66, C78, C84, C109 | Capacitor |  | LMK107B7105KAHT | 1
2 | 2.2K | R0402 | R80, R89 | Resistor |  | AC0402FR-072K2L | 1
6 | 2.2uF | C0603 | C95, C98, C117, C120, C125, C126 | Capacitor |  | CGA3E1X7R0J225K080AC | 1
2 | 2.4K | R0402 | R83, R87 | Resistor |  | AC0402FR-072K4L | 1
1 | 2.7K | R0402 | R72 | Resistor |  | AC0402FR-072K7L | 1
2 | 200 | R0402 | R55, R59 | Resistor |  | AC0402FR-07200RL | 1
12 | 200M/200V | R1206 | R4, R5, R6, R7, R8, R9, R10, R11, R12, R13, R14, R15 | Resistor |  | CRCW1206200MJPEAHR | 1
2 | 20K | R0402 | R64, R93 | Resistor |  | AC0402FR-0720KL | 1
1 | 20pF | C0402 | C65 | Capacitor |  | GCM1555C1H200JA16D | 1
1 | 22 | R0402 | R53 | Resistor |  | AC0402FR-0722RL | 1
4 | 220 | R0402 | R70, R74, R79, R85 | Resistor |  | AC0402FR-07220RL | 1
39 | 2200pF/250V | C0805 | C5, C6, C7, C8, C9, C10, C11, C12, C13, C14, C15, C16, C17, C21, C22, C23, C24,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 | Capacitor |  | C0805C222JAGACAUTO | 1
1 | 220pF/100V/5% | C0805 | C20 | Capacitor |  | C0805C221J1GACAUTO | 1
2 | 240 | R0402 | R78, R84 | Resistor |  | AC0402FR-07240RL | 1
4 | 27 | R0402 | R33, R34, R98, R99 | Resistor |  | AC0402FR-0727RL | 1
1 | 270 | R0402 | R54 | Resistor |  | AC0402FR-07270RL | 1
1 | 270K | R0402 | R62 | Resistor |  | AC0402FR-07270KL | 1
2 | 330 | R0402 | R69, R73 | Resistor |  | AC0402FR-07330RL | 1
1 | 33pF | C0402 | C134 | Capacitor |  | GCM1555C1H330FA16D | 1
1 | 3900pF/50V | C0805 | C19 | Capacitor |  | CGA4C2C0G1H392J060AA | 1
17 | 390K | R0402 | R3, R17, R18, R19, R20, R21, R22, R23, R24, R25, R26, R27, R28, R29, R39, R40, 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 | Resistor |  | AC0402FR-07390KL | 1
3 | 3pF | C0402 | C75, C80, C135 | Capacitor |  | GCM1555C1H3R0BA16D | 1
4 | 4.7uF | C0603 | C111, C121, C128, C130 | Capacitor |  | JMK107BJ475KAHT | 1
1 | 430 | R0402 | R75 | Resistor |  | AC0402FR-07430RL | 1
1 | 47K | R0402 | R51 | Resistor |  | AC0402FR-0747KL | 1
4 | 47M/150V | R0805 | R31, R32, R37, R38 | Resistor |  | RC0805JR-0747ML | 1
3 | 49.9 | R0402 | R45, R46, R48 | Resistor |  | AC0402FR-0749R9L | 1
2 | 4pF | C0402 | C79, C83 | Capacitor |  | GCM1555C1H4R0BA16D | 1
1 | 510 | R0402 | R50 | Resistor |  | AC0402FR-07510RL | 1
1 | 56 | R0402 | R60 | Resistor |  | AC0402FR-0756RL | 1
2 | 7.5pF | C0402 | C76, C77 | Capacitor |  | GCQ1555C1H7R5BB01D | 1
2 | 74AUP2G3404GW | SC70-6L | IC11, IC13 | Buffer plus inverter |  | 74AUP2G3404GW,125 | 1
1 | 74LVC1T45DCK | SC70-6L | IC1 | Level Translator |  | 74LVC1T45GW-Q100H | 1
1 | 750 | R0402 | R68 | Resistor |  | AC0402FR-07750RL | 1
2 | 8pF | C0402 | C63, C81 | Capacitor |  | GCM1555C1H8R0BA16D | 1
2 | AD8014ART | SOT23-5 | IC2, IC5 | Amplifier |  | AD8014ARTZ-REEL7 | 1
13 | BAS101S,215 | SOT23 | D2, D3, D4, D5, D6, D7, D8, D9, D10, D11, D12, D13, D14 | High voltage switching diodes |  | BAS101S,215 | 1
2 | BAV99W,115 | SC70-3L | D15, D16 | Dual Schottky Diodes |  | BAV99W,115 | 1
2 | U.FL-R-SMT-1(10) | HIROSE_U.FL-R-SMT-1 | J2, J3 | Coax connector |  | U.FL-R-SMT-1(10) | 1
1 | 3M-45216-220230 | 3M-45216-220230 | J1 | Header | 3M | 45216-220230 | 1
1 | ICE40UP5K-SG48I | QFN48 | IC9 | iCE40 Ultra FPGA SG48 version |  | ICE40UP5K-SG48I | 1
1 | INA199C2DCK | SC70-6L | IC12 | INA199 Low or High-Side Current Shunt Monitor |  | INA199C2DCKR | 1
1 | LTC2141IUP-12 | QFN64 | IC10 | ADC |  | LTC2141IUP-12 | 1
1 | MAX9013EUA | MSOP8 | IC3 | Comparator |  | MAX9013EUA+ | 1
1 | MLZ2012N101LT | L0805 | L13 | Inductor |  | MLZ2012N101LTD25 | 1
9 | MMZ1005A222ETD25 | L0402 | L2, L4, L6, L9, L10, L12, L14, L16, L17 | Chip bead |  | MMZ1005A222ETD25 | 1
7 | MMZ1005S601HTD25 | L0402 | L1, L7, L8, L11, L15, L18, L19 | Chip bead |  | MMZ1005S601ETD25 | 1
1 | SMAJ150A | DO214AC | D1 | TVS Diode, unidirectional |  | SMAJ150A | 1
1 | SN74AUC1G17DCK | SC70-5L | IC4 | Schmitt trigger buffer |  | SN74AUC1G17DCKR | 1
1 | STM32L552CCU | UFQFPN48 | IC8 | ARM Cortex-M33 MCU+FPU |  | STM32L552CCU6 | 1
2 | THS4551IRGT | LFCSP16 | IC6, IC7 | Amplifier |  | THS4551IRGTR | 1

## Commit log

2023-04-19 add V1.4PH design
